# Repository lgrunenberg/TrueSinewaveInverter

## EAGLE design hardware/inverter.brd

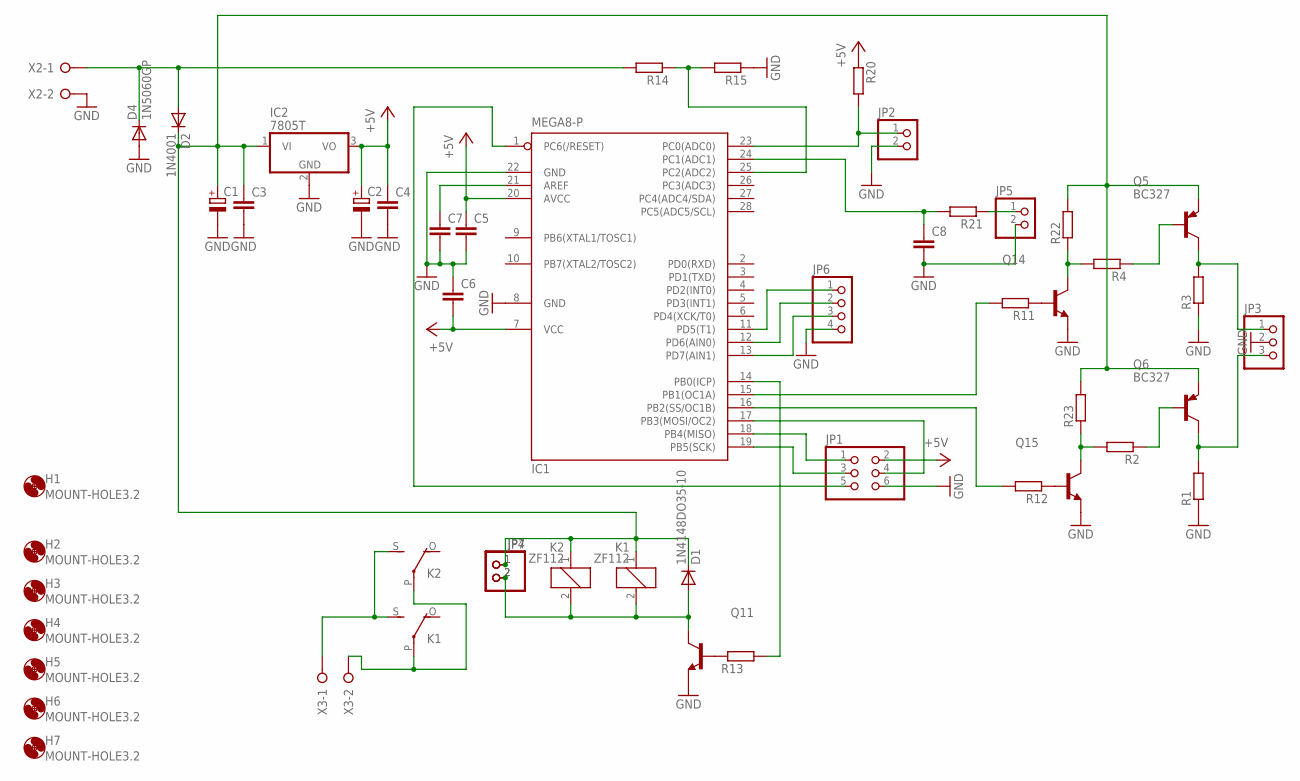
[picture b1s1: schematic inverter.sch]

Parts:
C1: CPOL-EUE7.5-16; E7,5-16
C2: CPOL-EUE2.5-6; E2,5-6
C3, C4, C5, C6, C7, C8: C-EU050-025X075; C050-025X075
D1: 1N4148DO35-10; DO35-10
D2: 1N4001; DO35-10
D4: 1N5060GP; DO15-12
H1, H2, H3, H4, H5, H6, H7: MOUNT-HOLE3.2; 3,2
IC1: MEGA8-P; DIL28-3
IC2: 7805T; TO220H
JP1: PINHD-2X3; 2X03
JP2, JP4, JP5, JP7: PINHD-1X2; 1X02
JP3: PINHD-1X3; 1X03
JP6: PINHD-1X4; 1X04
K1, K2: ZF112
Q5, Q6: BC327; TO92-EBC
Q11, Q14, Q15: BC547-NPN-TO92-CBE; TO92-CBE
R1, R3, R11, R12: R-EU_0207/5V; 0207/5V
R2, R4, R13, R21: R-EU_0207/2V; 0207/2V
R14, R15, R20, R22, R23: R-EU_0207/10; 0207/10
X2, X3: W237-02P; W237-132

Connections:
+5V: C2.+, C4.1, C5.1, C6.2, IC1.7 (VCC), IC1.20 (AVCC), IC2.3 (VO), JP1.2, R20.1
GND: C1.-, C2.-, C3.2, C4.2, C5.2, C6.1, C7.2, C8.2, D4.A, IC1.8 (GND), IC1.22 (GND), IC2.2 (GND), JP1.6, JP2.2, JP3.2, JP5.2, JP6.4, Q11.E, Q14.E, Q15.E, R1.1, R3.1, R15.1, X2.2
unnamed: JP5.1, R21.1
unnamed: Q6.B, R2.1
unnamed: Q5.B, R4.1
unnamed: JP3.1, Q5.C, R3.2
unnamed: IC1.25 (PC2(ADC2)), R14.1, R15.2
unnamed: IC1.13 (PD7(AIN1)), JP6.3
unnamed: JP3.3, Q6.C, R1.2
unnamed: Q15.C, R2.2, R23.1
unnamed: Q15.B, R12.1
unnamed: IC1.15 (PB1(OC1A)), R11.2
unnamed: IC1.16 (PB2(SS/OC1B)), R12.2
unnamed: C7.1, IC1.21 (AREF)
unnamed: D2.A, D4.C, R14.2, X2.1
unnamed: C1.+, C3.1, D1.C, D2.C, IC2.1 (VI), JP4.1, JP7.1, K1.1, K2.1, Q5.E, Q6.E, R22.2, R23.2
unnamed: C8.1, IC1.24 (PC1(ADC1)), R21.2
unnamed: D1.A, JP4.2, JP7.2, K1.2, K2.2, Q11.C
unnamed: Q11.B, R13.1
unnamed: K1.P, K2.P, X3.2
unnamed: IC1.12 (PD6(AIN0)), JP6.2
unnamed: IC1.18 (PB4(MISO)), JP1.1
unnamed: IC1.19 (PB5(SCK)), JP1.3
unnamed: IC1.17 (PB3(MOSI/OC2)), JP1.4
unnamed: IC1.1 (PC6(/RESET)), JP1.5
unnamed: IC1.11 (PD5(T1)), JP6.1
unnamed: K1.S, K2.S, X3.1
unnamed: Q14.B, R11.1
unnamed: IC1.23 (PC0(ADC0)), JP2.1, R20.2
unnamed: Q14.C, R4.2, R22.1
unnamed: IC1.14 (PB0(ICP)), R13.2

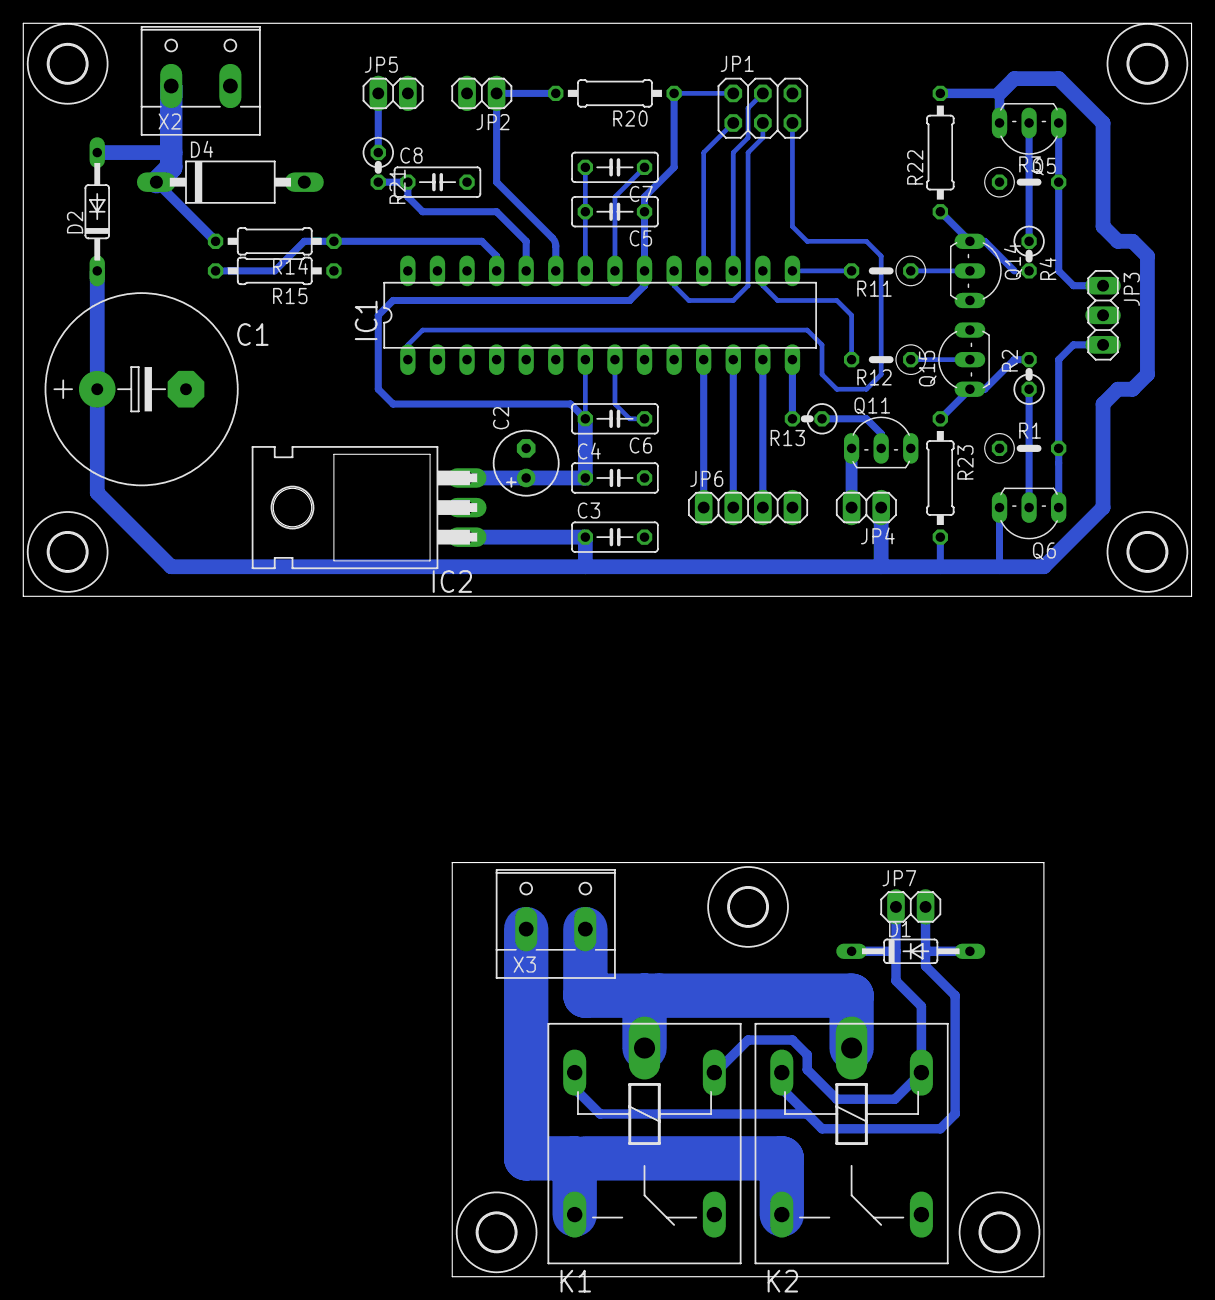
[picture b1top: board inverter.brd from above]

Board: 2 copper layers, 100.3 x 107.6 mm, 49 parts (0 on the bottom side), 31 nets.

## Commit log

2016-03-15 Added gitignore
